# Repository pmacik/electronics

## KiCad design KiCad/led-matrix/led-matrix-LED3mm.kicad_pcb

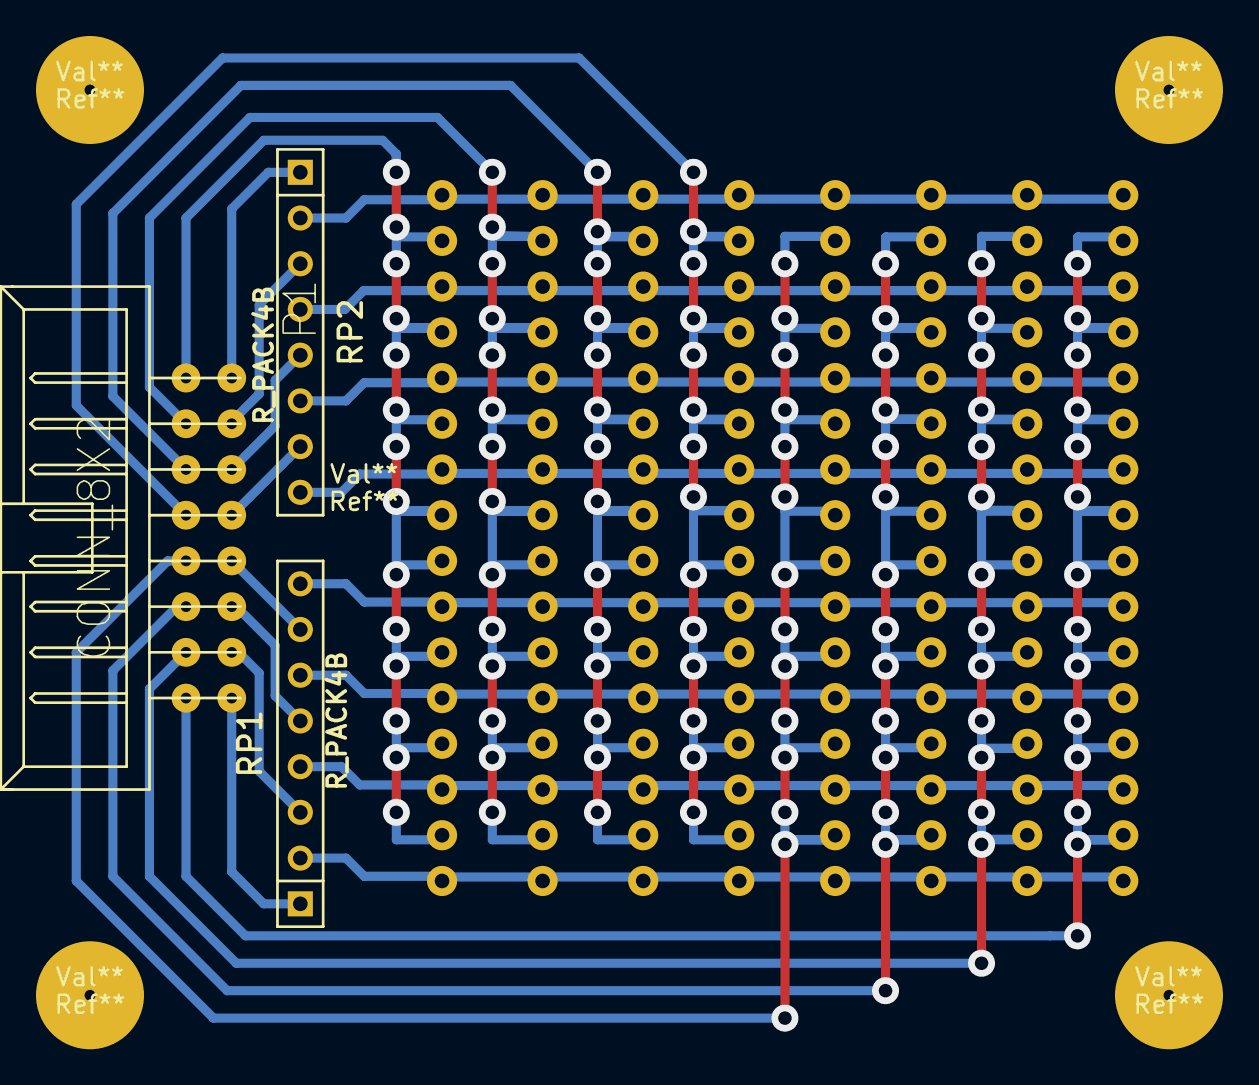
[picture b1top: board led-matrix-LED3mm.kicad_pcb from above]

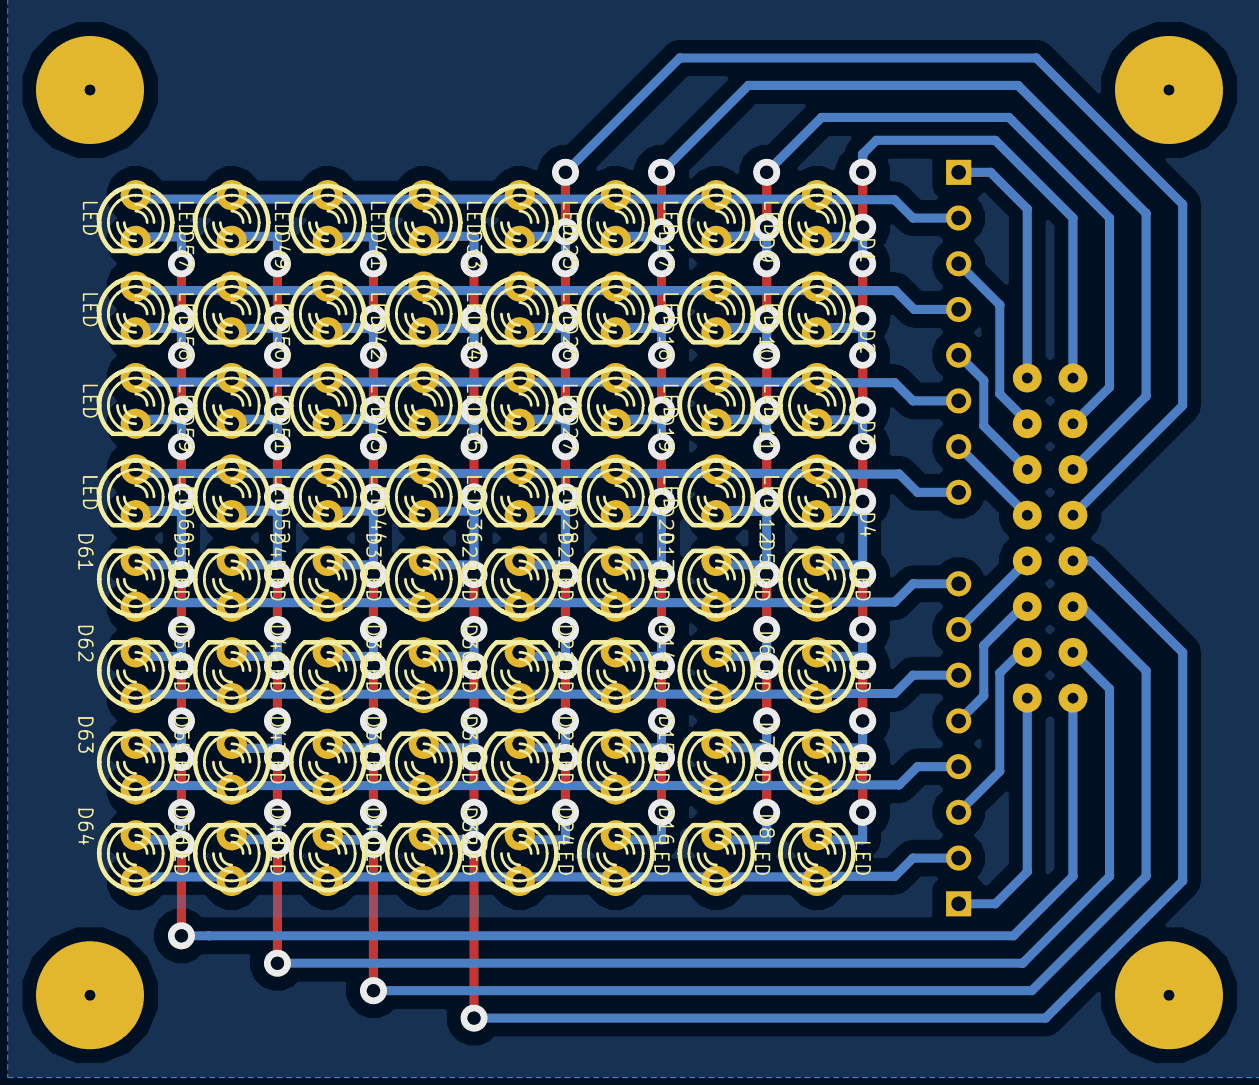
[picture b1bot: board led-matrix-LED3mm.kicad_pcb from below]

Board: 2 copper layers, 72 parts (64 on the bottom side), 24 nets.

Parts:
D1, D2, D3, D4, D5, D6, D7, D8, D9, D10, D11, D12, D13, D14, D15, D16, D17, D18, D19, D20, D21, D22, D23, D24, D25, D26, D27, D28, D29, D30, D31, D32, D33, D34, D35, D36, D37, D38, D39, D40, D41, D42, D43, D44, D45, D46, D47, D48, D49, D50, D51, D52, D53, D54, D55, D56, D57, D58, D59, D60, D61, D62, D63, D64: LED; LED-3MM
P1: CONN_8X2; VASCH8x2-90
RP1, RP2: R_PACK4B; r_pack4B
Ref**: Val**; pad
Ref**#2, Ref**#3, Ref**#4, Ref**#5: Val**; pad

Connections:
unnamed: D17.2, D18.2, D19.2, D20.2, D21.2, D22.2, D23.2, D24.2, P1.5
unnamed: D9.2, D10.2, D11.2, D12.2, D13.2, D14.2, D15.2, D16.2, P1.3
unnamed: D1.2, D2.2, D3.2, D4.2, D5.2, D6.2, D7.2, D8.2, P1.1
unnamed: D8.1, D16.1, D24.1, D32.1, D40.1, D48.1, D56.1, D64.1, RP1.2
unnamed: P1.10, RP1.7
unnamed: P1.12, RP1.5
unnamed: P1.14, RP1.3
unnamed: P1.16, RP1.1
unnamed: P1.8, RP2.7
unnamed: P1.6, RP2.5
unnamed: P1.4, RP2.3
unnamed: P1.2, RP2.1
unnamed: D25.2, D26.2, D27.2, D28.2, D29.2, D30.2, D31.2, D32.2, P1.7
unnamed: D57.2, D58.2, D59.2, D60.2, D61.2, D62.2, D63.2, D64.2, P1.15
unnamed: D49.2, D50.2, D51.2, D52.2, D53.2, D54.2, D55.2, D56.2, P1.13
unnamed: D41.2, D42.2, D43.2, D44.2, D45.2, D46.2, D47.2, D48.2, P1.11
unnamed: D33.2, D34.2, D35.2, D36.2, D37.2, D38.2, D39.2, D40.2, P1.9
unnamed: D1.1, D9.1, D17.1, D25.1, D33.1, D41.1, D49.1, D57.1, RP2.2
unnamed: D7.1, D15.1, D23.1, D31.1, D39.1, D47.1, D55.1, D63.1, RP1.4
unnamed: D2.1, D10.1, D18.1, D26.1, D34.1, D42.1, D50.1, D58.1, RP2.4
unnamed: D4.1, D12.1, D20.1, D28.1, D36.1, D44.1, D52.1, D60.1, RP2.8
unnamed: D6.1, D14.1, D22.1, D30.1, D38.1, D46.1, D54.1, D62.1, RP1.6
unnamed: D5.1, D13.1, D21.1, D29.1, D37.1, D45.1, D53.1, D61.1, RP1.8
unnamed: D3.1, D11.1, D19.1, D27.1, D35.1, D43.1, D51.1, D59.1, RP2.6
